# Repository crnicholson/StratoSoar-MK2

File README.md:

# StratoSoar MK2 - UAVs For the Masses

<!-- **TL;DR**: The StratoSoar project is a low-cost, lightweight UAV designed to be dropped from a weather balloon  at any altitude, aiming for autonomous, efficient flight to selected GPS coordinates. The hope is to get a UAV platform in the hands of educators, researchers, and hobbyists alike since StratoSoar is much smaller, lighter, and cheaper than conventional UAVs.  -->

**TL:DR**: The StratoSoar project is a low-cost, lightweight Unmanned Aerial Vechile (UAV) designed for deployment from a weather balloon at various altitudes, aiming for autonomous and efficient flight to designated GPS coordinates. By offering a more affordable, compact, and lightweight alternative to conventional UAVs, StratoSoar aims to empower educators, researchers, and hobbyists with an accessible platform for exploration and experimentation. 

## Watch The Video

<!-- **WORK IN PROGRESS** - This project is still in the works. I don't recommend using it yet because it has the potential of being dangerous.

**NEW** - Writing code and making the PCB. 

**STATE as of 7/1/24** - Just starting development! -->

 | 
-- | --
<i>StratoSoar glider.</i> | <i>StratoSoar MK2.0 circuit board.</i>

## What Is the StratoSoar Project?

StratoSoar is a low-power, adaptive UAV that is dropped from a weather balloon at approximately 5,000 feet, with plans to reach even higher altitudes soon. The main goal of StratoSoar is to fly to selected GPS coordinates efficiently or choose a closer, more realistic landing site without human interaction. The current aim for StratoSoar is to operate on a single 600 mAh 15 gram LiPo battery for a 10+ hour flight. 

## Now, What Is a UAV?

UAVs, or Unmanned Aerial Vehicles, are autonomous aircraft, usually in the form of planes or drones. They have many applications, such as [delivering medicine, food, and supplies](https://www.flyzipline.com/) to remote areas, participating in aerial combat with the military, and conducting aerial imaging.

### Common Types of UAVs Include:

- Quadcopter (typical drones)
- Fixed-wing aircraft (like StratoSoar)

## StratoSoar vs. Conventional UAVs

### Traditional UAVs Are Typically:

- Large (5-15 meter wingspan)
- Heavy (2-20 kg)
- Expensive ($10,000-10,000,000 USD)
- Closed source and propietary

### StratoSoar Aims to Overcome These Limitations With:

- Weight: less than 250 grams
- Wingspan: 80 cm
- Cost: less than $150 USD
- Open source and accesible

## What Are the Uses of StratoSoar?

I'm currently considering two main concepts: an educational kit for students and hobbyists or a platform designed to study the aerodynamics of the stratosphere, a field with limited existing resources. Additionally, I'm exploring other ideas such as reusable radiosondes, systems for remote delivery of medicine and parcels, and advanced atmospheric monitoring solutions.

<!-- ## What Includes the StratoSoar Project? What Are the Different Parts of it?

StratoSoar has many different parts, and they all combine to make this project. 

- **Code** - All of the code directory, and the programs needed to run it. These include the main `.ino`s and the accompanying `.cpp` and `.h` files, along with the test files for the IMU and GPS.
- **PCB** - The circuit board is the basis of this project, it interfaces the code with the glider. StratoSoar includes the circuit board files and the schematics and everything needed to build a PCB.
- **3D Files** - StratoSoar requires some 3D printed parts to function, but these files also serve as an interactive build guide. StratoSoar includes the 3D files needed to print parts for the glider and the 3D files to assemble the glider.
- **Media** - The images and such of StratoSoar. 
- **Cutdown Mechanism** - This is the thing that helps you release the glider from the balloon payload - or whatever you want to drop it from. This includes all of the above things but will be in a separate GitHub repository.  -->

## How Does StratoSoar Work at a High Level?

<!-- StratoSoar is attached to a weather balloon via the cutdown mechanism. Once the balloon reaches the desired altitude, the cutdown mechanism drops the glider. The glider then descends, steering its way to specified coordinates. 

StratoSoar takes pride in being highly configurable and hackable, so there are many ways you change how it comes down built into the code. 

StratoSoar uses data from an IMU that goes through a Kalman filter to receive accurate AHRS, or Attitude Heading Reference System. This can tell StratoSoar the pitch, yaw, and roll of the glider. Then, StratoSoar integrates a GPS module to get the GPS coordinates. Both the GPS and the AHRS are used to compute the azimuth to find the turning angle of the glider. The turning angle tells the glider how much it needs to turn to be facing the correct yaw that will get the glider to the target location. Additionally, an algorithm is used to get the distance between the glider location's and the target location. 

With the turning angle computed, a PID mechanism is used to control the servo attached to the rudder of the glider. This PID mechanism learn from it's mistakes and can accurately aim the glider in the correct direction. 

Additionally, the glider beacons it's location at a configurable interval with LoRa for tracking. It also allows for a camera module to be added on to take photos and video. 

The glider will fly to the selected coordinates, and depending on the user configuration, will either spiral down or release a parachute above the coordinates once it has reached them to safely descend. Additionally, if the glider is too low in altitude, prior to the flight the user can enter closer coordinates as backup landing locations.  -->

StratoSoar MK2 is an advanced autonomous glider designed to operate at high altitudes, such as those reached by weather balloons. The glider is attached to a weather balloon via a cutdown mechanism. Once the balloon reaches the desired altitude, the cutdown mechanism releases the glider, initiating its descent. The glider then navigates autonomously to specified coordinates, using a combination of sensors, advanced algorithms, and low-power electronics.

### Core Components and Functionality:

- **Autopilot System**:
    - **GPS and IMU Integration**: StratoSoar uses a custom GPS module and an IMU, both designed for low-power operation. The IMU data is processed through a Kalman filter to provide accurate Attitude Heading Reference System (AHRS) data, including pitch, yaw, and roll. This information, combined with GPS coordinates, enables precise navigation.
    - **Servo Control with PID**: A PID control mechanism governs the rudder’s servo, ensuring precise adjustments to the glider's course based on real-time feedback.
    - **Hackability**: StratoSoar is designed to be highly configurable and hackable. Users can customize its descent strategy, whether by spiral descent, parachute deployment, or alternative landing locations. The codebase is modular, allowing for easy modifications or the addition of new features.
   
- **PCB Design**:
    - **StratoSoar MK3 PCB**: The main PCB, optimized for power efficiency, size, and cost, integrates over 100 components, managing the various systems onboard.
    - **Additional PCBs**: Supporting PCBs, such as those for the GPS module, switching regulator, and IMU, are designed for specific tasks, enhancing the glider's overall functionality.

### Operation and Recovery:

Upon release from the weather balloon, StratoSoar begins its guided descent following waypoints or single target coordinate. It calculates the optimal flight path using its GPS and AHRS data, making real-time adjustments to its trajectory through the PID-controlled servo system. Depending on user configurations, the glider can either glide smoothly to the target coordinates, initiate a spiral descent, or deploy a parachute for a safe landing.

If the glider's altitude drops below a certain threshold, backup landing coordinates can be used to ensure a safe recovery. Throughout the flight, the glider’s location is continuously transmitted, allowing for easy tracking and recovery.

<!-- ## File System and More Project Info

I'm only listing the key items, leaving out all the unessecary stuff. This should give you a general sense of the project and all it's features. Note that this is also only stuff I did during Hack Club Arcade.

- `Code/autopilot`: (5000 lines of code!)
    - `autopilot.ino`: The script that ties all of these files together.
    - `gps.cpp`: GPS code custom-made for low-power.
    - `waypoint.cpp`: Custom waypoint flight with advanced turning.
    - `lora.cpp`: LoRa communications with complex forward error correction.
    - `sd.cpp` + `eeprom.cpp`: Data logging in a low-power manner.
    - `servo.cpp`: Ultra low-power servo functions.
    - `bme280.cpp`: Weather data sensor.
    - `imu.cpp`: An interial measurement unit running a Kalman filter.
- `Code/groundStation`: 
    - `groundStation.ino`: The code for the receiving station of the LoRa telemetry, uses ESP32 and HTTP requests to communicate with the server, also locally logs data. 
    - `uploader/flaskUploader.py`: A Flask server that uses an API to put all the data on SondeHub. 
- `Code/camera`: Utilization of a low-power camera module and Python scripts for conversion.
- `Code/calculator`: Python script to parametrically create flying wing glider. 
- `PCB/StratoSoar-MK3.0`: The main PCB consisting of over 100 components, optimized for power, size, and cost.
- `PCB/gpsBreakout`: A PCB designed for testing a cheap, $2 Chinese GPS module.
- `PCB/loRa`: The ground station to receive the glider's data. 
- `PCB/camera`: A breakout board for a low-power camera module. 
- `PCB/imuBreakout`: One of the first breakout boards made for a new Interial Measurement Unit. 
- `3D Files/cardboardGlider`: Parametric Fusion 360 desgin for a folding origami glider. 
- `3D Files/StratoSoar Rev2 v36`: High efficieny glider. -->

## A Quick Note on MK1, MK2, Naming, and Revisions

StratoSoar MK1 was the precursor and the spark to StratoSoar MK2. StratoSoar MK1 was officially developed from October 1st to July 30th, although StratoSoar MK2 was unofficially being worked on in the months of March through June. StratoSoar MK1 failed to fly autonomously, and it also failed to release from the balloon. Major upgrades have been made since then.

StratoSoar MK2 officially started on October 1st, and has now ended. It was a success. 

My newer version, which you should check out, officially started on June 1st. It is called StratoSoar MK3 and will end in quite some time when I launch it from a weather balloon. A new major revision (eg. MK4) will come out every time when I release the glider from the balloon in the Summer. After the Summer, work on the next revision begins, with many updates and new features. 

<!-- A new sub-revision (for lack of better word) comes out every time I make a new PCB. For example, my first version of my PCB was MK2.0. At the time of writing, the current version of StratoSoar is MK2.1. A new version of 3D model is denoted by the Rev number. Rev starts at 0. 0 and 1 are not shown in this repo because they didn't turn out very good. The physical gliders are denoted by the 3D model number. Sometimes a small change is made with glider so the name of the glider is Rev x.x, for example. Sometimes the same happens with the 3D model, again it would be x.x. To put this in practice, the final glider may be MK2.5 Rev 7.3.1. The code has no version history in the way the 3D models and the PCB do. -->

Also, I use "we" a lot in this writing. This usually refers to myself or this project, but it also refers to my small team over at New England Weather Balloon Society.

One last thing. When I refer to StratoSoar, I am referring to the project as a whole, but more specifically, the most recent version. 

<!-- ## Watch my Talk About StratoSoar MK2 The North East HamXpo! -->

## Is This Legal?
Yes! During flight, the ground operator has no ***direct*** control over the flight path, i.e. via a radio. Because of this, and it being unpowered, it qualifies as a free flight glider. Free flight gliders have very little regulations. You can think of them as a paper airplane. 

## Can I Buy a Kit or a Complete Product?

Currently, StratoSoar is not available to purchase online as a kit or complete product. We have plans in the next few years to release a kit for schools, education centers, hobbyists and a complete product for industry at an affordable price. You are welcome to make one in the mean time!

## How Can I Make One? Are There Docs?

One of the goals of StratoSoar was to make an affordable and open source system for anyone to perform stratospheric research, so all the files are available for free. This means that you can construct StratoSoar from scratch. **A guide to do this will be available soon.**

<!-- It is still in the works, but you can check out `DOCS.md` under the `Docs` folder.**  -->

## Helpful Sources and Credits

I'm in the midst of compiling this.

## Cutdown Mechanism

[See my other WIP GitHub repo.](https://github.com/crnicholson/Cutdown-Mechanism)

## Funding and Support

We currently have <u>**very**</u> limited funding to complete this project. We would **love any donations or sponsorships** we could get to elevate (no pun intended) this project to the next level. If you don't want to donate, but want to help out, we would love your support with other areas of this project. Reach out to me if you have interest at:

- [newbsballoons@gmail.com](mailto:newbsballoons@gmail.com) (organization email, recommended).

- [charlienicholsonr@gmail.com](mailto:charlienicholsonr@gmail.com) (personal email).

## Special Thanks

This project would not be possible without the following individuals:

- Max Kendall (W0MXX) for working closely together with me.

- Mike Malis for helping with the design of the glider. 

- Brett Miwa for schematic review, PCB design, electrical theory, and boost converter circuitry design.

- Bob Phinney (K5TEC) for providing NEST and securing funding.

- Mark Jessop (VK5QI) for answering all of my questions.

- Mike Hojnowski (KD2EAT) for PCB design and hardware/software debugging.

- Paul Hamilton for helping me with FAA regulations.

- My parents!

And these entities:

- Hack Club, for providing support for projects like this. 

- New England Sci-Tech (NEST) for providing a maker space to work, funding, and hosting NEWBS.

- New England Weather Balloon Society (NEWBS) for expertise and the opportunity.

- Bagel Fund, for providing funding. 

## Affiliate Programs and Projects

- **Hack Club** - Hack Club is a non-profit designed for teenagers that provides support for projects like this. 
- **NEWBS** - Max and Seth Kendall of NEWBS, or New England Weather Balloon Society, are helping me launch my project from a balloon. They are dedicated to helping people in New England launch weather balloons. 
- **New England Sci-Tech** - Bob Phinney of NEST is hosting NEWBS. NEST is a great maker space. If you are in the Greater Boston Area, go check them out!
- **StratoScience** - This is the official class that I'm in helping me launch my project. This is a high altitude engineering class for teens. Check them out if your are in the Greater Boston area!

## Still Have Questions?

Do you have any questions? Are the docs incomplete and you want to ask anything? Do you just want to say hi (or how cool my project is!)?

Reach out to me at [charlienicholsonr@gmail.com](mailto:charlienicholsonr@gmail.com).

## License

Both the software and documentation are under the [GNU GPL v3 license](https://choosealicense.com/licenses/gpl-3.0/). The hardware and the 3D files are under the [CERN Open Hardware Licence Version 2 - Strongly Reciprocal](https://choosealicense.com/licenses/cern-ohl-s-2.0/). The media is under the [CC BY 4.0 DEED](https://creativecommons.org/licenses/by/4.0/).

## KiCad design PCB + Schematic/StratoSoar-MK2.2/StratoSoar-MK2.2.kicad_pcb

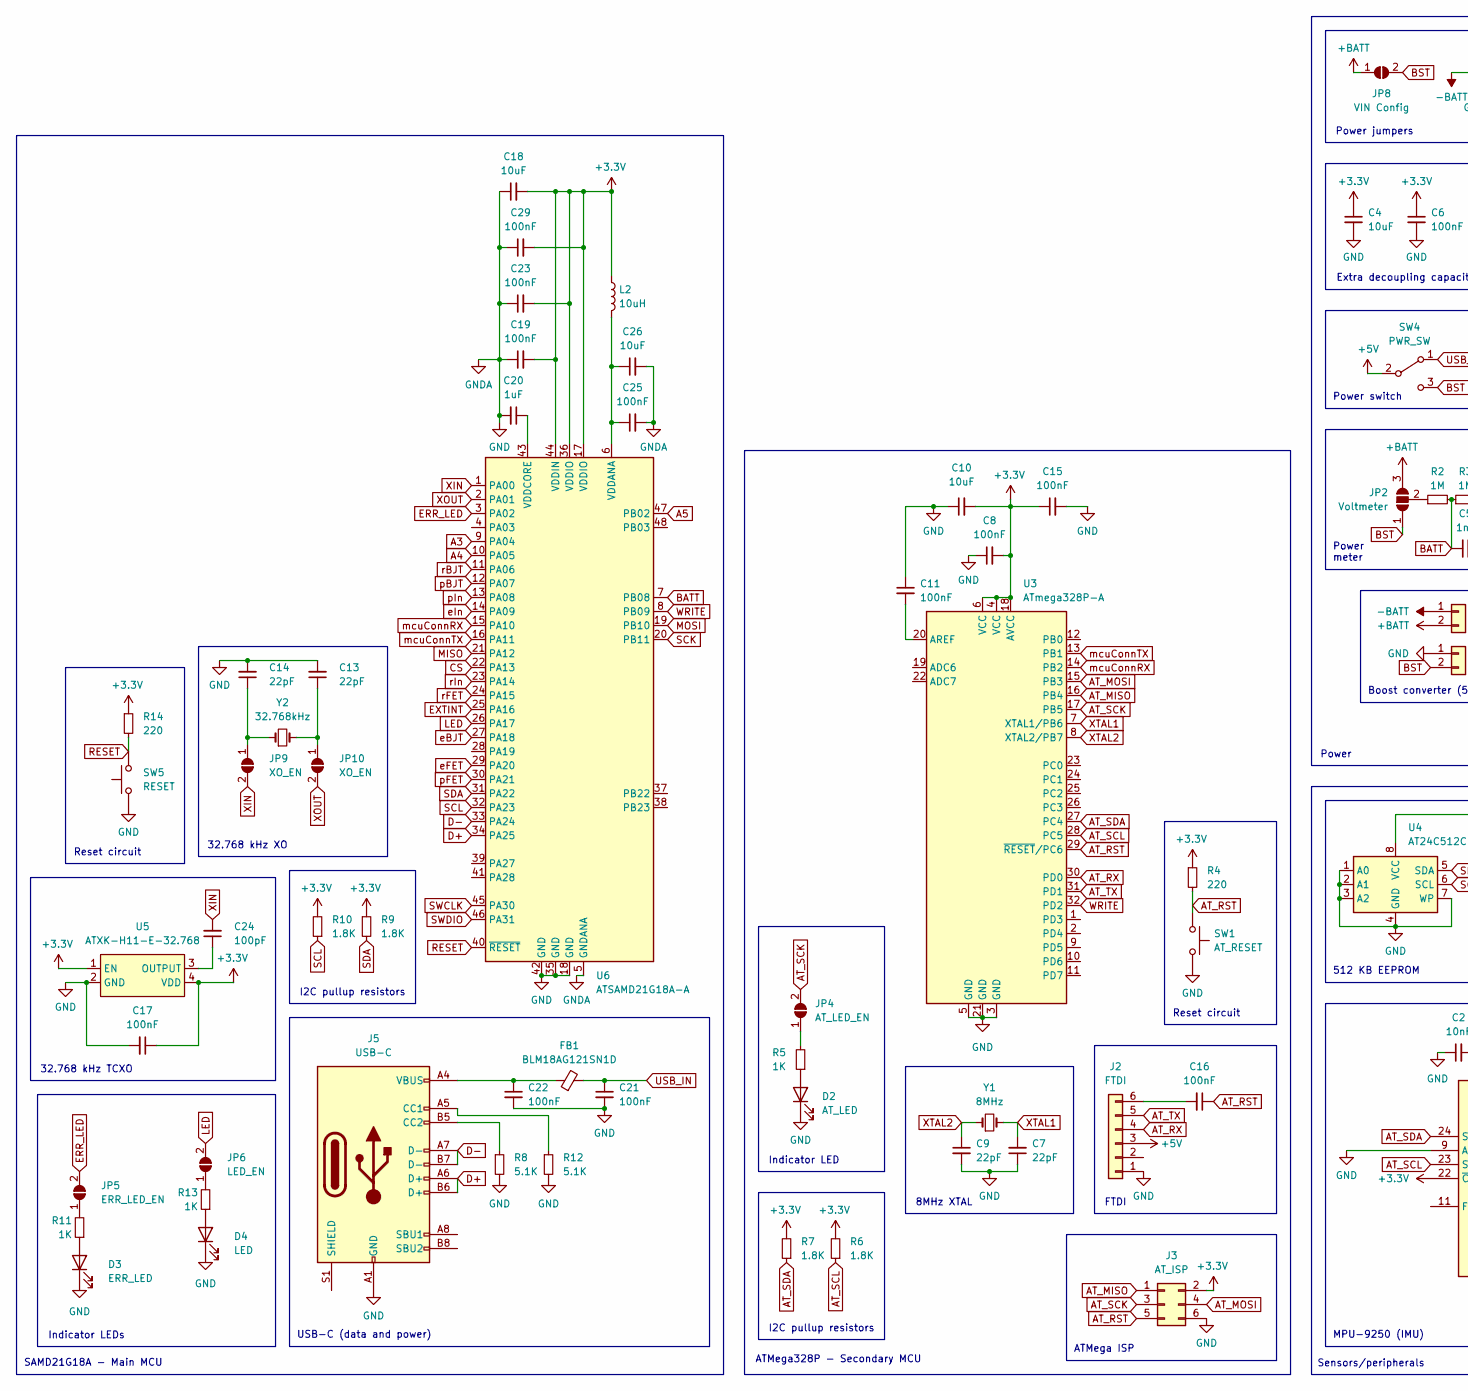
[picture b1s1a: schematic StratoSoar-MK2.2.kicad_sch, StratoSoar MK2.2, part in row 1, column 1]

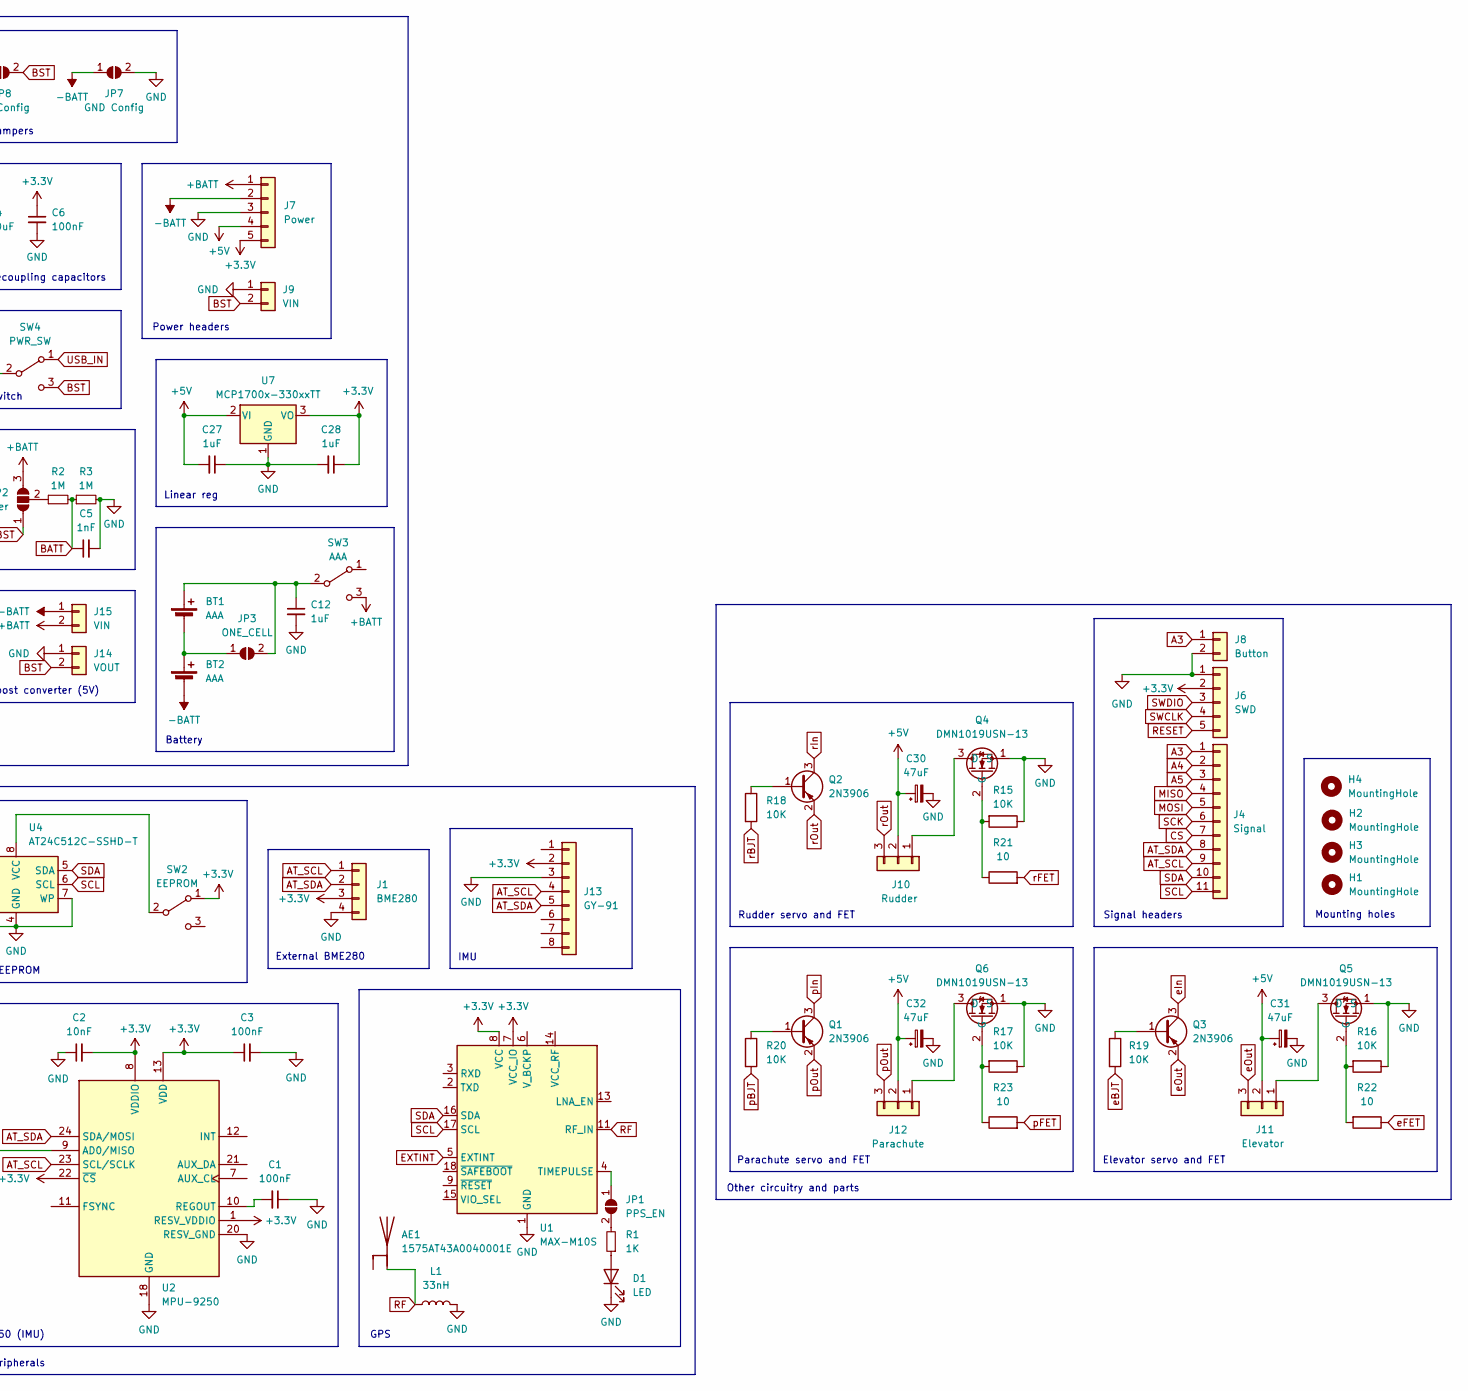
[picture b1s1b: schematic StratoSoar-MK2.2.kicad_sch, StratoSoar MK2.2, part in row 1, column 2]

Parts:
AE1: 1575AT43A0040001E; ANT_1575AT_JOT-L
BT1, BT2: AAA; BatteryHolder_BK-82
C1, C3, C6, C8, C11, C15, C16, C17, C19, C21, C22, C23, C25, C29: 100nF; C_0805_2012Metric_Pad1.18x1.45mm_HandSolder
C2: 10nF; C_0805_2012Metric_Pad1.18x1.45mm_HandSolder
C4, C10, C18, C26: 10uF; C_0805_2012Metric_Pad1.18x1.45mm_HandSolder
C5: 1nF; C_0805_2012Metric_Pad1.18x1.45mm_HandSolder
C7, C9, C13, C14: 22pF; C_0805_2012Metric_Pad1.18x1.45mm_HandSolder
C12, C20, C27, C28: 1uF; C_0805_2012Metric_Pad1.18x1.45mm_HandSolder
C24: 100pF; C_0805_2012Metric_Pad1.18x1.45mm_HandSolder
C30, C31, C32: 47uF; CP_EIA-3528-21_Kemet-B
D1, D4: LED; LED_0805_2012Metric_Pad1.15x1.40mm_HandSolder
D2: AT_LED; LED_0805_2012Metric_Pad1.15x1.40mm_HandSolder
D3: ERR_LED; LED_0805_2012Metric_Pad1.15x1.40mm_HandSolder
FB1: BLM18AG121SN1D; R_0603_1608Metric_Pad0.98x0.95mm_HandSolder
H1, H2, H3, H4: MountingHole; MountingHole_2.2mm_M2
J1: BME280; PinHeader_1x04_P2.54mm_Vertical
J2: FTDI; PinHeader_1x06_P2.54mm_Vertical
J3: AT_ISP; PinHeader_2x03_P2.54mm_Vertical
J4: Signal; PinHeader_1x11_P2.54mm_Vertical
J5: USB-C; USB_C_Receptacle_GCT_USB4105-xx-A_16P_TopMnt_Horizontal
J6: SWD; PinHeader_1x05_P2.54mm_Vertical
J7: Power; PinHeader_1x05_P2.54mm_Vertical
J8: Button; PinHeader_1x02_P2.54mm_Vertical
J9: VIN; PinHeader_1x02_P2.54mm_Vertical
J10: Rudder; PinHeader_1x03_P2.54mm_Vertical
J11: Elevator; PinHeader_1x03_P2.54mm_Vertical
J12: Parachute; PinHeader_1x03_P2.54mm_Vertical
J13: GY-91; 1x08_SMD_Pads
J14: VOUT; 1x02_SMD_Pads
J15: VIN; 1x02_SMD_Pads
JP1: PPS_EN; SolderJumper-2_P1.3mm_Open_RoundedPad1.0x1.5mm
JP2: Voltmeter; SolderJumper-3_P1.3mm_Open_RoundedPad1.0x1.5mm_NumberLabels
JP3: ONE_CELL; SolderJumper-2_P1.3mm_Open_RoundedPad1.0x1.5mm
JP4: AT_LED_EN; SolderJumper-2_P1.3mm_Open_RoundedPad1.0x1.5mm
JP5: ERR_LED_EN; SolderJumper-2_P1.3mm_Open_RoundedPad1.0x1.5mm
JP6: LED_EN; SolderJumper-2_P1.3mm_Open_RoundedPad1.0x1.5mm
JP7: GND Config; SolderJumper-2_P1.3mm_Open_RoundedPad1.0x1.5mm
JP8: VIN Config; SolderJumper-2_P1.3mm_Open_RoundedPad1.0x1.5mm
JP9, JP10: XO_EN; SolderJumper-2_P1.3mm_Open_RoundedPad1.0x1.5mm
L1: 33nH; L_0805_2012Metric_Pad1.15x1.40mm_HandSolder
L2: 10uH; L_0805_2012Metric_Pad1.15x1.40mm_HandSolder
Q1, Q2, Q3: 2N3906; SOT-23-3
Q4, Q5, Q6: DMN1019USN-13; SC-59_Handsoldering
R1, R5, R11, R13: 1K; R_0805_2012Metric_Pad1.20x1.40mm_HandSolder
R2, R3: 1M; R_0805_2012Metric_Pad1.20x1.40mm_HandSolder
R4, R14: 220; R_0805_2012Metric_Pad1.20x1.40mm_HandSolder
R6, R7, R9, R10: 1.8K; R_0805_2012Metric_Pad1.20x1.40mm_HandSolder
R8, R12: 5.1K; R_0805_2012Metric_Pad1.20x1.40mm_HandSolder
R15, R16, R17, R18, R19, R20: 10K; R_0805_2012Metric_Pad1.20x1.40mm_HandSolder
R21, R22, R23: 10; R_0805_2012Metric_Pad1.20x1.40mm_HandSolder
SW1: AT_RESET; SW_SPST_CK_RS282G05A3
SW2: EEPROM; SW_SPDT_PCM12
SW3: AAA; SW_SPDT_PCM12
SW4: PWR_SW; SW_SPDT_PCM12
SW5: RESET; SW_SPST_CK_RS282G05A3
U1: MAX-M10S; ublox_MAX
U2: MPU-9250; InvenSense_QFN-24_3x3mm_P0.4mm
U3: ATmega328P-A; TQFP-32_7x7mm_P0.8mm
U4: AT24C512C-SSHD-T; SOIC-8_3.9x4.9mm_P1.27mm
U5: ATXK-H11-E-32.768; Crystal_SMD_Abracon_ABM8AIG-4Pin_3.2x2.5mm
U6: ATSAMD21G18A-A; TQFP-48_7x7mm_P0.5mm
U7: MCP1700x-330xxTT; SOT-89-3
Y1: 8MHz; Crystal_HC18-U_Vertical
Y2: 32.768kHz; Crystal_C26-LF_D2.1mm_L6.5mm_Horizontal

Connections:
+3.3V: C2.2, C3.1, C4.1, C6.1, C8.2, C10.2, C15.1, C17.1, C18.2, C19.2, C23.2, C28.1, C29.2, J1.3, J3.2, J6.2, J7.5, J13.2, L2.1, R4.1, R6.2, R7.2, R9.1, R10.2, R14.1, SW2.1 (A), U1.7 (VCC_IO), U1.8 (VCC), U2.1 (RESV_VDDIO), U2.8 (VDDIO), U2.13 (VDD), U2.22 (~CS), U3.4 (VCC), U3.6 (VCC), U3.18 (AVCC), U5.1 (EN), U5.4 (VDD), U6.17 (VDDIO), U6.36 (VDDIO), U6.44 (VDDIN), U7.3 (VO)
+5V: C27.2, C30.1, C31.1, C32.1, J2.3, J7.4, J10.2, J11.2, J12.2, SW4.2 (B), U7.2 (VI)
+BATT: J7.1, J15.2, JP2.3 (B), JP8.1 (A), SW3.3 (C)
-BATT: BT2.2 (-), J7.2, J15.1, JP7.1 (A)
A3: J4.1, J8.1, U6.9 (PA04)
A4: J4.2, U6.10 (PA05)
A5: J4.3, U6.47 (PB02)
AT_MISO: J3.1, U3.16 (PB4)
AT_MOSI: J3.4, U3.15 (PB3)
AT_RST: C16.1, J3.5, R4.2, SW1.1, U3.29 (~RESET/PC6)
AT_RX: J2.4, U3.30 (PD0)
AT_SCK: J3.3, JP4.2 (B), U3.17 (PB5)
AT_SCL: J1.1, J4.9, J13.4, R6.1, U2.23 (SCL/SCLK), U3.28 (PC5)
AT_SDA: J1.2, J4.8, J13.5, R7.1, U2.24 (SDA/MOSI), U3.27 (PC4)
AT_TX: J2.5, U3.31 (PD1)
BATT: C5.1, R2.2, R3.1, U6.7 (PB08)
BST: J9.2, J14.2, JP2.1 (A), JP8.2 (B), SW4.3 (C)
CS: J4.7, U6.22 (PA13)
D+: J5.A6 (D+), J5.B6 (D+), U6.34 (PA25)
D-: J5.A7 (D-), J5.B7 (D-), U6.33 (PA24)
ERR_LED: JP5.2 (B), U6.3 (PA02)
EXTINT: U1.5 (EXTINT), U6.25 (PA16)
GND: C1.1, C2.1, C3.2, C4.2, C5.2, C6.2, C7.1, C8.1, C9.2, C10.1, C11.1, C12.2, C13.2, C14.2, C15.2, C17.2, C18.1, C19.1, C20.2, C21.2, C22.2, C23.1, C25.2, C26.2, C27.1, C28.2, C29.1, C30.2, C31.2, C32.2, D1.1 (K), D2.1 (K), D3.1 (K), D4.1 (K), J1.4, J2.1, J3.6, J5.A1 (GND), J5.A12 (GND), J5.B1 (GND), J5.B12 (GND), J6.1, J7.3, J8.2, J9.1, J13.3, J14.1, JP7.2 (B), L1.2, Q4.1 (S), Q5.1 (S), Q6.1 (S), R3.2, R8.2, R12.2, R15.1, R16.1, R17.1, SW1.2, SW5.1, U1.1 (GND), U1.10 (GND), U1.12 (GND), U2.9 (AD0/MISO), U2.18 (GND), U2.20 (RESV_GND), U3.3 (GND), U3.5 (GND), U3.21 (GND), U4.1 (A0), U4.2 (A1), U4.3 (A2), U4.4 (GND), U4.7 (WP), U5.2 (GND), U6.5 (GNDANA), U6.18 (GND), U6.35 (GND), U6.42 (GND), U7.1 (GND)
LED: JP6.2 (B), U6.26 (PA17)
MISO: J4.4, U6.21 (PA12)
MOSI: J4.5, U6.19 (PB10)
unnamed: BT1.1 (+), C12.1, JP3.2 (B), SW3.2 (B)
unnamed: BT1.2 (-), BT2.1 (+), JP3.1 (A)
unnamed: C22.1, FB1.1, J5.A4 (VBUS), J5.A9 (VBUS), J5.B4 (VBUS), J5.B9 (VBUS)
unnamed: D1.2 (A), R1.1
unnamed: D2.2 (A), R5.1
unnamed: D3.2 (A), R11.1
unnamed: D4.2 (A), R13.1
unnamed: C16.2, J2.6
unnamed: J5.A5 (CC1), R12.1
unnamed: J5.B5 (CC2), R8.1
unnamed: J10.1, Q4.3 (D)
unnamed: J11.1, Q5.3 (D)
unnamed: J12.1, Q6.3 (D)
unnamed: JP1.1 (A), U1.4 (TIMEPULSE)
unnamed: JP1.2 (B), R1.2
unnamed: JP2.2 (C), R2.1
unnamed: JP4.1 (A), R5.2
unnamed: JP5.1 (A), R11.2
unnamed: JP6.1 (A), R13.2
unnamed: C14.1, JP9.1 (A), Y2.1
unnamed: C13.1, JP10.1 (A), Y2.2
unnamed: Q1.1 (B), R20.1
unnamed: Q2.1 (B), R18.1
unnamed: Q3.1 (B), R19.1
unnamed: Q4.2 (G), R15.2, R21.1
unnamed: Q5.2 (G), R16.2, R22.2
unnamed: Q6.2 (G), R17.2, R23.1
unnamed: SW2.2 (B), U4.8 (VCC)
unnamed: C1.2, U2.10 (REGOUT)
unnamed: C11.2, U3.20 (AREF)
unnamed: C24.1, U5.3 (OUTPUT)
unnamed: C25.1, C26.1, L2.2, U6.6 (VDDANA)
unnamed: C20.1, U6.43 (VDDCORE)
RESET: J6.5, R14.2, SW5.2, U6.40 (~RESET)
RF: AE1.1 (FEED), L1.1, U1.11 (RF_IN)
SCK: J4.6, U6.20 (PB11)
SCL: J4.11, R10.1, U1.17 (SCL), U4.6 (SCL), U6.32 (PA23)
SDA: J4.10, R9.2, U1.16 (SDA), U4.5 (SDA), U6.31 (PA22)
SWCLK: J6.4, U6.45 (PA30)
SWDIO: J6.3, U6.46 (PA31)
USB_IN: C21.1, FB1.2, SW4.1 (A)
WRITE: U3.32 (PD2), U6.8 (PB09)
XIN: C24.2, JP9.2 (B), U6.1 (PA00)
XOUT: JP10.2 (B), U6.2 (PA01)
XTAL1: C7.2, U3.7 (XTAL1/PB6), Y1.2
XTAL2: C9.1, U3.8 (XTAL2/PB7), Y1.1
eBJT: R19.2, U6.27 (PA18)
eFET: R22.1, U6.29 (PA20)
eIn: Q3.3 (C), U6.14 (PA09)
eOut: J11.3, Q3.2 (E)
mcuConnRX: U3.14 (PB2), U6.15 (PA10)
mcuConnTX: U3.13 (PB1), U6.16 (PA11)
pBJT: R20.2, U6.12 (PA07)
pFET: R23.2, U6.30 (PA21)
pIn: Q1.3 (C), U6.13 (PA08)
pOut: J12.3, Q1.2 (E)
rBJT: R18.2, U6.11 (PA06)
rFET: R21.2, U6.24 (PA15)
rIn: Q2.3 (C), U6.23 (PA14)
rOut: J10.3, Q2.2 (E)

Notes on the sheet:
Battery
Indicator LEDs
IMU
ATMega328P - Secondary MCU
Other circuitry and parts
Power jumpers
8MHz XTAL
I2C pullup resistors
External BME280
FTDI
Power meter
Elevator servo and FET
ATMega ISP
Linear reg
Power
Power headers
Mounting holes
Reset circuit
Parachute servo and FET
SAMD21G18A - Main MCU
Boost converter (5V)
USB-C (data and power)
32.768 kHz TCXO
MPU-9250 (IMU)
32.768 kHz XO
Sensors/peripherals
Extra decoupling capacitors
GPS
512 KB EEPROM
Rudder servo and FET
Power switch
Signal headers
Indicator LED

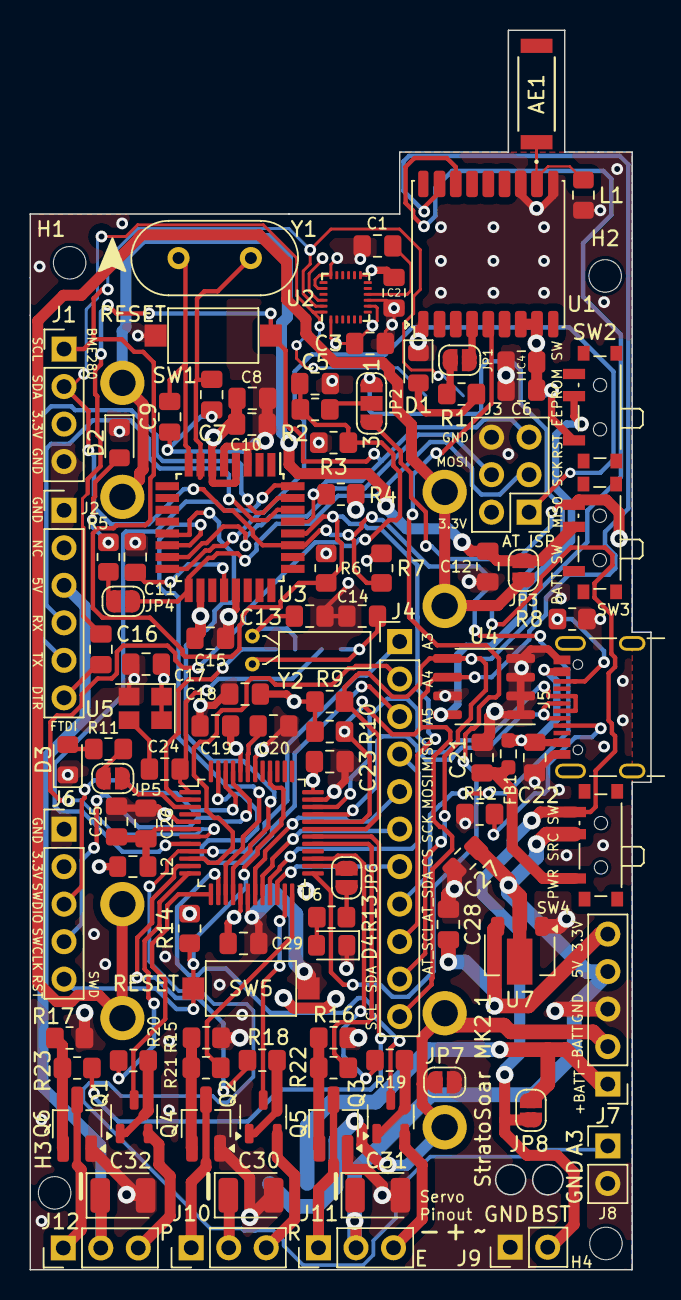
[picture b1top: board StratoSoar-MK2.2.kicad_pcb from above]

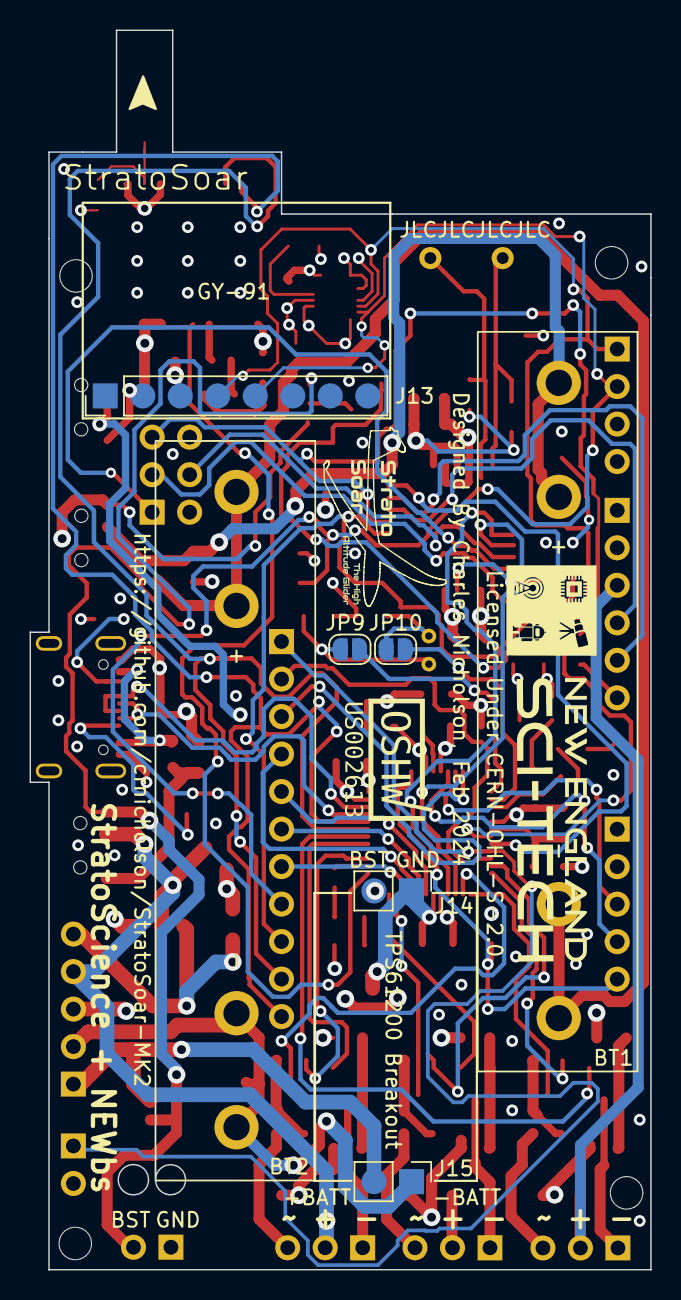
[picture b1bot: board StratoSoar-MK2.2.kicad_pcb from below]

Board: 4 copper layers, 42.0 x 83.9 mm, 114 parts (7 on the bottom side), 86 nets.

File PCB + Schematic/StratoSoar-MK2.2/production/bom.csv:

Designator,Footprint,Quantity,Value,LCSC Part #
AE1,ANT_1575AT_JOT-L,1,1575AT43A0040001E,
"BT1, BT2",BatteryHolder_BK-82,2,AAA,
"C1, C11, C15, C16, C17, C19, C21, C22, C23, C25, C29, C3, C6, C8",0805,14,100nF,
"C10, C18, C26, C4",0805,4,10uF,
"C12, C20, C27, C28",0805,4,1uF,
"C13, C14, C7, C9",0805,4,22pF,
C2,0805,1,10nF,
C24,0805,1,100pF,
"C30, C31, C32",CP_EIA-3528-21_Kemet-B,3,47uF,
C5,0805,1,1nF,
"D1, D4",0805,2,LED,
D2,0805,1,AT_LED,
D3,0805,1,ERR_LED,
FB1,0603,1,BLM18AG121SN1D,
"H1, H2, H3, H4",MountingHole_2.2mm_M2,4,MountingHole,
J1,PinHeader_1x04_P2.54mm_Vertical,1,BME280,
J10,PinHeader_1x03_P2.54mm_Vertical,1,Rudder,
J11,PinHeader_1x03_P2.54mm_Vertical,1,Elevator,
J12,PinHeader_1x03_P2.54mm_Vertical,1,Parachute,
J13,1x08_SMD_Pads,1,GY-91,
J14,1x02_SMD_Pads,1,VOUT,
J15,1x02_SMD_Pads,1,VIN,
J2,PinHeader_1x06_P2.54mm_Vertical,1,FTDI,
J3,PinHeader_2x03_P2.54mm_Vertical,1,AT_ISP,
J4,PinHeader_1x11_P2.54mm_Vertical,1,Signal,
J5,USB_C_Receptacle_GCT_USB4105-xx-A_16P_TopMnt_Horizontal,1,USB-C,
J6,PinHeader_1x05_P2.54mm_Vertical,1,SWD,
J7,PinHeader_1x05_P2.54mm_Vertical,1,Power,
J8,PinHeader_1x02_P2.54mm_Vertical,1,Button,
J9,PinHeader_1x02_P2.54mm_Vertical,1,VIN,
JP1,SolderJumper-2_P1.3mm_Open_RoundedPad1.0x1.5mm,1,PPS_EN,
"JP10, JP9",SolderJumper-2_P1.3mm_Open_RoundedPad1.0x1.5mm,2,XO_EN,
JP3,SolderJumper-2_P1.3mm_Open_RoundedPad1.0x1.5mm,1,ONE_CELL,
JP4,SolderJumper-2_P1.3mm_Open_RoundedPad1.0x1.5mm,1,AT_LED_EN,
JP5,SolderJumper-2_P1.3mm_Open_RoundedPad1.0x1.5mm,1,ERR_LED_EN,
JP6,SolderJumper-2_P1.3mm_Open_RoundedPad1.0x1.5mm,1,LED_EN,
L1,0805,1,33nH,
L2,0805,1,10uH,
"Q1, Q2, Q3",SOT-23-3,3,2N3906,
"Q4, Q5, Q6",SC-59_Handsoldering,3,DMN1019USN-13,
"R1, R11, R13, R5",0805,4,1K,
"R10, R6, R7, R9",0805,4,1.8K,
"R12, R8",0805,2,5.1K,
"R14, R4",0805,2,220,
"R15, R16, R17, R18, R19, R20",0805,6,10K,
"R2, R3",0805,2,1M,
"R21, R22, R23",0805,3,10,
SW1,SW_SPST_CK_RS282G05A3,1,AT_RESET,
SW2,SW_SPDT_PCM12,1,EEPROM,
SW3,SW_SPDT_PCM12,1,AAA,
SW4,SW_SPDT_PCM12,1,PWR_SW,
SW5,SW_SPST_CK_RS282G05A3,1,RESET,
U1,ublox_MAX,1,MAX-M10S,
U2,InvenSense_QFN-24_3x3mm_P0.4mm,1,MPU-9250,
U3,TQFP-32_7x7mm_P0.8mm,1,ATmega328P-A,
U4,SOIC-8_3.9x4.9mm_P1.27mm,1,AT24C512C-SSHD-T,
U5,Crystal_SMD_Abracon_ABM8AIG-4Pin_3.2x2.5mm,1,ATXK-H11-E-32.768,
U6,TQFP-48_7x7mm_P0.5mm,1,ATSAMD21G18A-A,
U7,SOT-89-3,1,MCP1700x-330xxTT,
Y1,Crystal_HC18-U_Vertical,1,8MHz,
Y2,Crystal_C26-LF_D2.1mm_L6.5mm_Horizontal,1,32.768kHz,

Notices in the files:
PCB + Schematic/StratoSoar-MK2.2/StratoSoar-MK2.2.kicad_pcb:
Licensed Under CERN-OHL-S-2.0
